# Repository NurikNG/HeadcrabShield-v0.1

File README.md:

# HeadcrabShield-v0.1
KiCAD HeadcrabShield for my heater. <br>
Works in winter 2019-2020. Without inputs for buttons. <br>
Software is in HeaterControl repo. <br>

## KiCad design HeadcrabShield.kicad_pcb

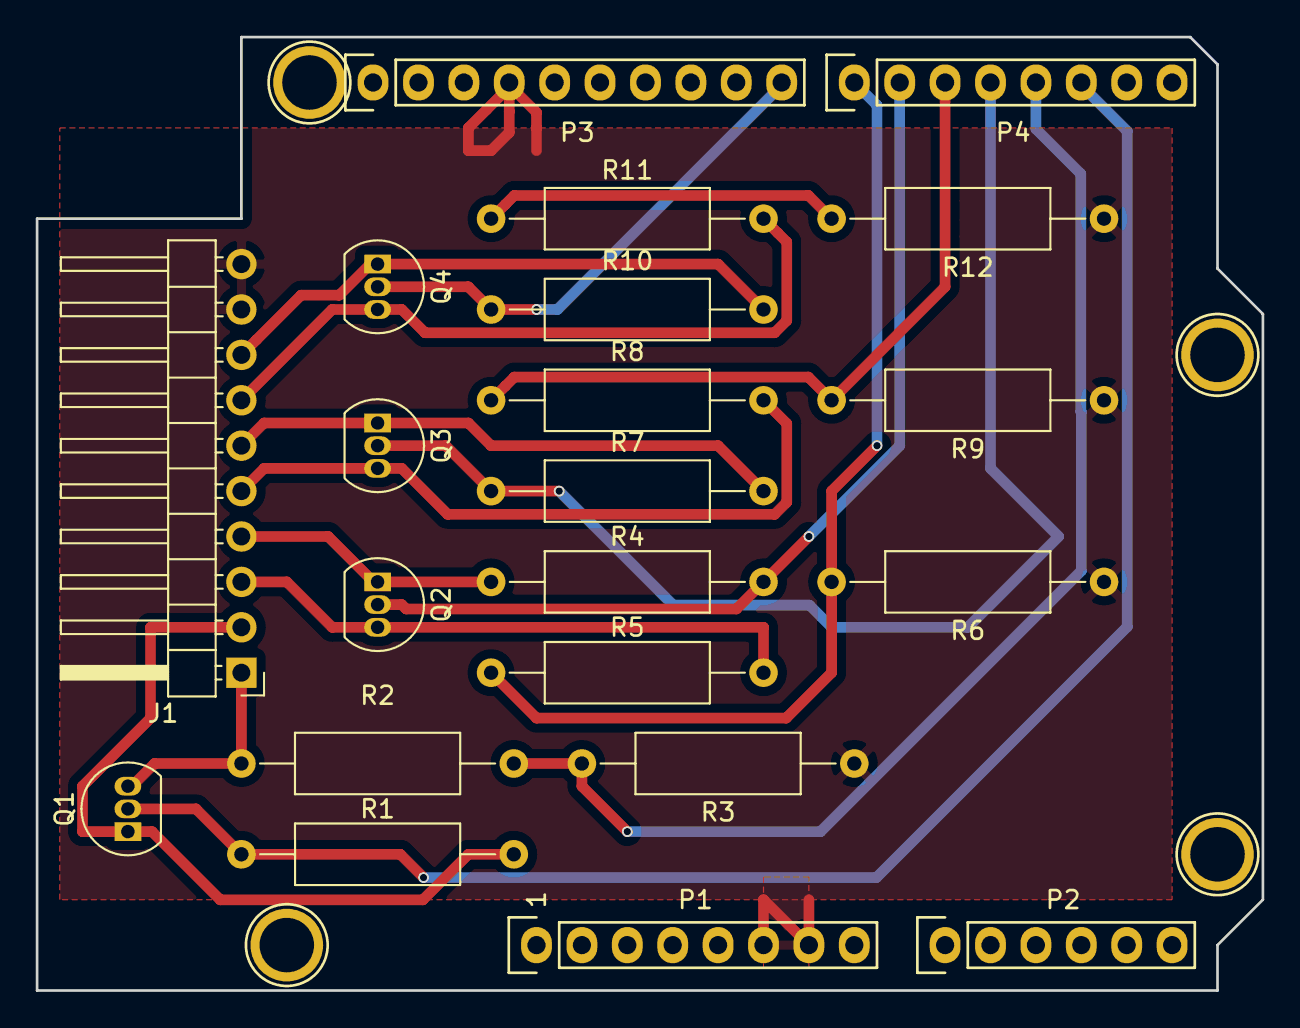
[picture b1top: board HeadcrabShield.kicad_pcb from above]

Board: 2 copper layers, 68.6 x 53.3 mm, 25 parts (0 on the bottom side), 17 nets.

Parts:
J1: Conn_01x10; PinHeader_1x10_P2.54mm_Horizontal
P1: Power; Socket_Strip_Arduino_1x08
P2: Analog; Socket_Strip_Arduino_1x06
P3: Digital; Socket_Strip_Arduino_1x10
P4: Digital; Socket_Strip_Arduino_1x08
P5, P6, P7, P8: CONN_01X01; Arduino_1pin
Q1, Q2, Q3, Q4: ZVN0545A; TO-92_Inline
R1, R4, R7, R10: 4.7K; R_Axial_DIN0309_L9.0mm_D3.2mm_P15.24mm_Horizontal
R2, R5, R8, R11: 10K; R_Axial_DIN0309_L9.0mm_D3.2mm_P15.24mm_Horizontal
R3, R6, R9, R12: 20K; R_Axial_DIN0309_L9.0mm_D3.2mm_P15.24mm_Horizontal

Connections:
/2: P4.6, Q1.2, R1.1
/3: P4.5, R2.1, R3.2
/4: P4.4, Q3.2, R7.1
/5: P4.3, R8.1, R9.2
/6: P4.2, Q2.2, R4.1
/7: P4.1, R5.1, R6.2
/8: P3.10, Q4.2, R10.1
/9: R11.1, R12.2
/B1D: J1.1, Q1.3, R2.2
/B1GND: J1.2, Q1.1, R1.2
/B2D: J1.3, Q2.3, R5.2
/B2GND: J1.4, Q2.1, R4.2
/B3D: J1.5, Q3.3, R8.2
/B3GND: J1.6, Q3.1, R7.2
/B4D: J1.7, Q4.3, R11.2
/B4GND: J1.8, Q4.1, R10.2
GND: J1.9, J1.10, P1.6, P1.7, P3.4, R3.1, R6.1, R9.1, R12.1

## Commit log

2019-12-24 Add files via upload
    v1
